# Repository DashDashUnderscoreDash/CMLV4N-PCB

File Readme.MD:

# **CMLV4N**

CMLV4N is an STM32 12u V4N style PCB with leafspring tadpole mounting featuring forced Cherry ML support

The goal of this PCB is to have a 40% keyboard that uses Cherry ML switches harvested from a Cherry G84-4100.

### PLEASE ENSURE YOU VERIFY THE SPACEBAR IS LARGE ENOUGH!!!! There are multiple models you can use for donor boards and some have too small of spacebar.

Due to the uneven u sizing on Cherry ML the enter key does not fill that entire area. The stabilizer positions for the enter also do not work as they are for a larger sized keycap. This is a compromise that needed to be made to make the layout work and a combination of skill issue. The stabilizer position on the enter does not work as the footprint is the incorrect size. Apologies!

~~Available~~ Sold out at [Dashkeebs](https://dashkeebs.bigcartel.com/product/cmlv4n-pcb) as of 10/1/26

### In this repo you will find:
```
- Layout options
- Images of PCB
- VIAL firmware
- STEP model of PCB
- Edgecuts of PCB
- Complete KiCad project
- Case files (STEP format)
```

VIAL firmware commissioned by [Moinboards.](https://moinboards.de/) Thank you again so much!

### KLC layout

### PCB images

### Case image

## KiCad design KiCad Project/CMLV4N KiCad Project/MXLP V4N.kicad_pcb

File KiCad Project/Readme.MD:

# **CMLV4N KiCad Project**

This is my first fully open source KiCad project!

Made in KiCad 9 as it's working well for me and I'm afraid to upgrade and break things

As of 10/3/26 everything uploads to JLC with no errors less needing to orient some components on JLCPCB
<br>
<br>
<br>
I'm not sure if anything else should be put in this readme, so apologies if any information is missing. Feel free to start an issue or DM me on Discord. Username: dashdashunderscoredash
<br>
<br>
<br>
Due to skill issue, when making production files, some components are not oriented correctly. When placing the components in JLC you will need to change:
__ __
- U4: Transient voltage suppressor
__ __
- U3: Over current protection
__ __

### Incorrect orientation

### Corrected orientation

<br>
<br>
<br>
**Credit:** Leafspring tadpole mount by HaiZeus. Thank you so much for sharing these with me, letting me use on my designs, and helping me learning to design in general. [Please check out his store](https://www.haikey.design/), he's a very talented designer!

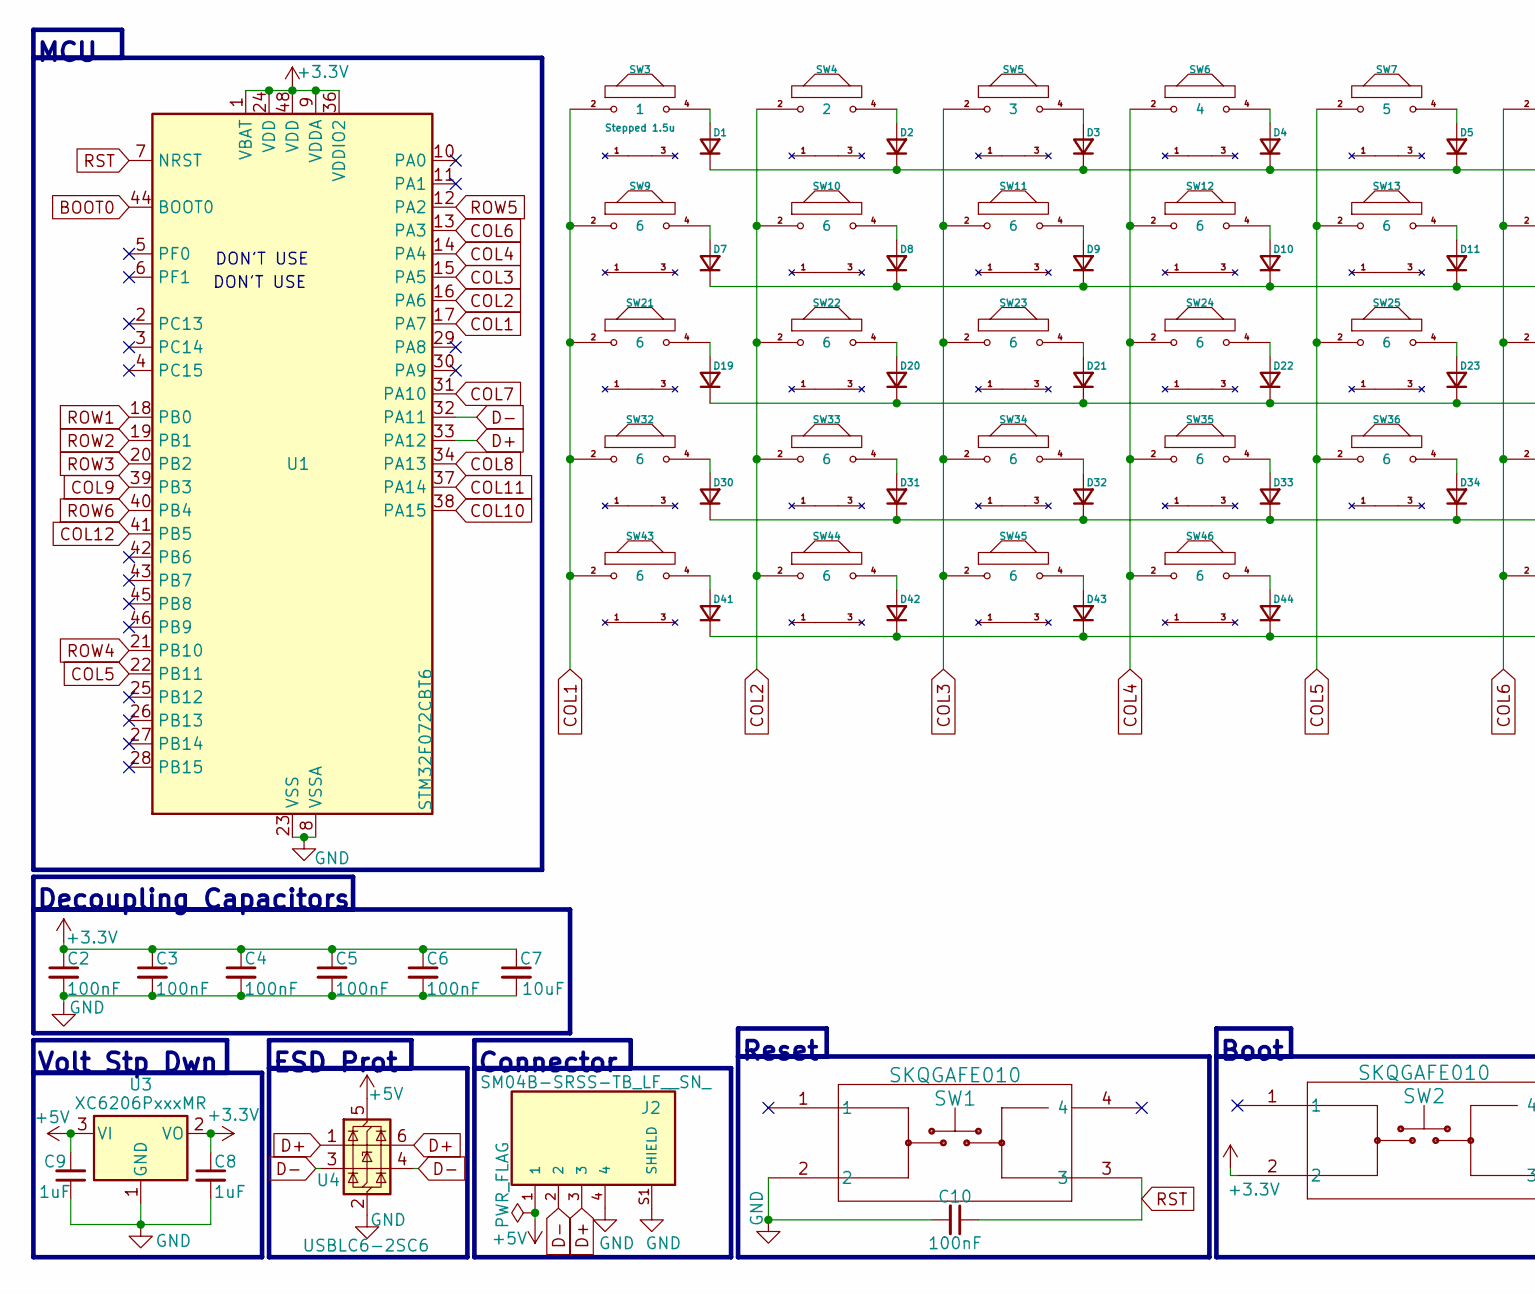
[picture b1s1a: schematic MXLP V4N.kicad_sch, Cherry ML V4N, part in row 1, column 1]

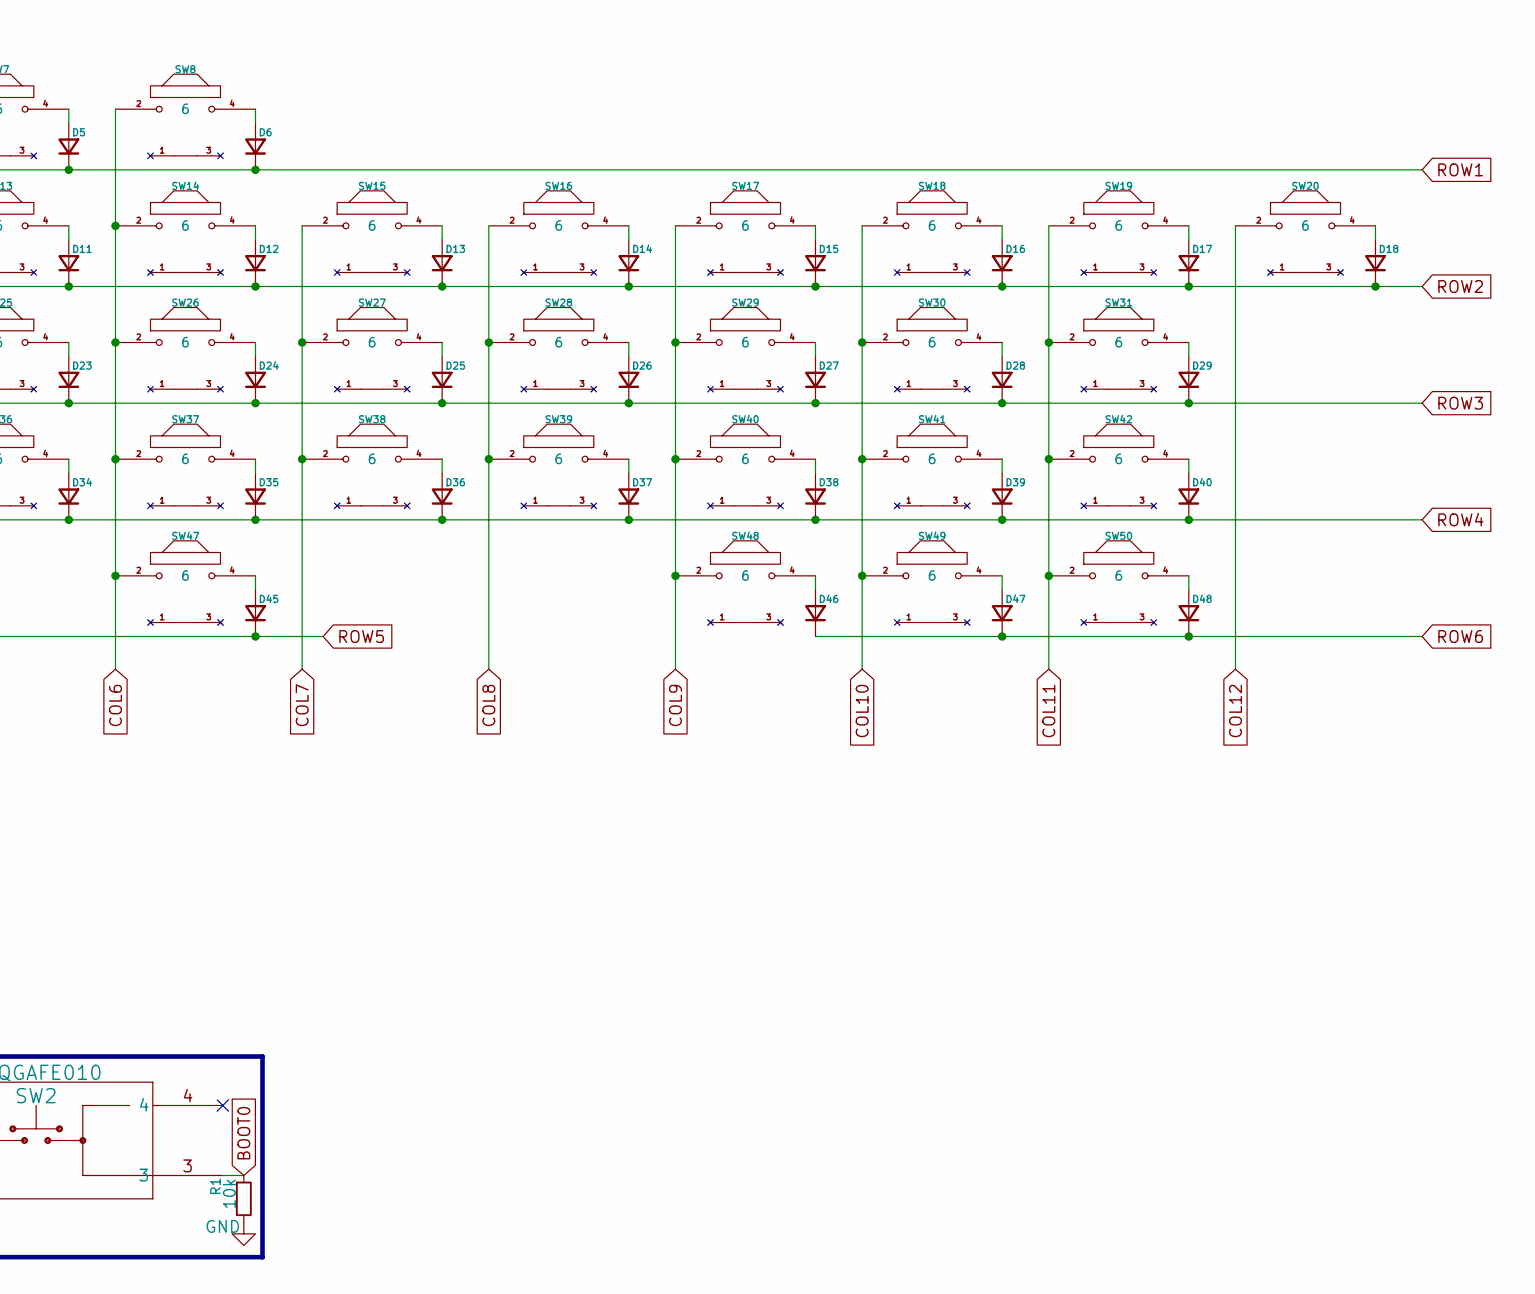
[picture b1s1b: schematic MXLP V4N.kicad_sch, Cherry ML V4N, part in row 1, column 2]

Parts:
C2, C3, C4, C5, C6: 100nF; C_0603_1608Metric; LCSC # C49678
C7: 10uF; C_0603_1608Metric; LCSC # C15850
C8, C9: 1uF; C_0603_1608Metric; LCSC # C28323
C10: 100nF; C_0603_1608Metric
D1, D2, D3, D4, D5, D6, D7, D8, D9, D10, D11, D12, D13, D14, D15, D16, D17, D18, D19, D20, D21, D22, D23, D24, D25, D26, D27, D28, D29, D30, D31, D32, D33, D34, D35, D36, D37, D38, D39, D40, D41, D42, D43, D44, D45, D46, D47, D48: D_Small; D_0603_1608Metric
J2: SM04B-SRSS-TB_LF__SN_; JST-SR-4; LCSC # C51940130
R1: 10k; R_0603_1608Metric; LCSC # C17414
SW1, SW2: SKQGAFE010; SW4_SKQGAFE010_ALPS; LCSC # C202424
SW3: 1; SW_Cherry_ML_1u_Centred_Wired_Correctly
SW4: 2; SW_Cherry_ML_1u_Centred_Wired_Correctly
SW5: 3; SW_Cherry_ML_1u_Centred_Wired_Correctly
SW6: 4; SW_Cherry_ML_1u_Centred_Wired_Correctly
SW7: 5; SW_Cherry_ML_1u_Centred_Wired_Correctly
SW8, SW9, SW10, SW11, SW12, SW13, SW14, SW15, SW16, SW17, SW18, SW19, SW20, SW21, SW22, SW23, SW24, SW25, SW26, SW27, SW28, SW29, SW30, SW31, SW32, SW33, SW34, SW35, SW36, SW37, SW38, SW39, SW40, SW41, SW42, SW43, SW44, SW45, SW46, SW47, SW48, SW49, SW50: 6; SW_Cherry_ML_1u_Centred_Wired_Correctly
U1: STM32F072CBT6; LQFP-48_7x7mm_P0.5mm; LCSC # C81720
U3: XC6206PxxxMR; SOT-23-3; LCSC # C5446
U4: USBLC6-2SC6; SOT-23-6; LCSC # C2687116

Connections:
+3.3V: C2.1, C3.1, C4.1, C5.1, C6.1, C7.1, C8.1, SW2.2, U1.1 (VBAT), U1.9 (VDDA), U1.24 (VDD), U1.36 (VDDIO2), U1.48 (VDD), U3.2 (VO)
+5V: C9.2, J2.1, U3.3 (VI), U4.5 (VBUS)
BOOT0: R1.1, SW2.3, U1.44 (BOOT0)
COL1: SW3.2, SW9.2, SW21.2, SW32.2, SW43.2, U1.17 (PA7)
COL2: SW4.2, SW10.2, SW22.2, SW33.2, SW44.2, U1.16 (PA6)
COL3: SW5.2, SW11.2, SW23.2, SW34.2, SW45.2, U1.15 (PA5)
COL4: SW6.2, SW12.2, SW24.2, SW35.2, SW46.2, U1.14 (PA4)
COL5: SW7.2, SW13.2, SW25.2, SW36.2, U1.22 (PB11)
COL6: SW8.2, SW14.2, SW26.2, SW37.2, SW47.2, U1.13 (PA3)
COL7: SW15.2, SW27.2, SW38.2, U1.31 (PA10)
COL8: SW16.2, SW28.2, SW39.2, U1.34 (PA13)
COL9: SW17.2, SW29.2, SW40.2, SW48.2, U1.39 (PB3)
COL10: SW18.2, SW30.2, SW41.2, SW49.2, U1.38 (PA15)
COL11: SW19.2, SW31.2, SW42.2, SW50.2, U1.37 (PA14)
COL12: SW20.2, U1.41 (PB5)
D+: J2.3, U1.33 (PA12), U4.1 (I/O1), U4.6 (I/O1)
D-: J2.2, U1.32 (PA11), U4.3 (I/O2), U4.4 (I/O2)
GND: C2.2, C3.2, C4.2, C5.2, C6.2, C7.2, C8.2, C9.1, C10.2, J2.4, J2.S1 (SHIELD), J2.S2 (SHIELD), R1.2, SW1.2, U1.8 (VSSA), U1.23 (VSS), U1.35 (VSS), U1.47 (VSS), U3.1 (GND), U4.2 (GND)
unnamed: D1.2 (A), SW3.4
unnamed: D2.2 (A), SW4.4
unnamed: D3.2 (A), SW5.4
unnamed: D4.2 (A), SW6.4
unnamed: D5.2 (A), SW7.4
unnamed: D6.2 (A), SW8.4
unnamed: D7.2 (A), SW9.4
unnamed: D8.2 (A), SW10.4
unnamed: D9.2 (A), SW11.4
unnamed: D10.2 (A), SW12.4
unnamed: D11.2 (A), SW13.4
unnamed: D12.2 (A), SW14.4
unnamed: D13.2 (A), SW15.4
unnamed: D14.2 (A), SW16.4
unnamed: D15.2 (A), SW17.4
unnamed: D16.2 (A), SW18.4
unnamed: D17.2 (A), SW19.4
unnamed: D18.2 (A), SW20.4
unnamed: D19.2 (A), SW21.4
unnamed: D20.2 (A), SW22.4
unnamed: D21.2 (A), SW23.4
unnamed: D22.2 (A), SW24.4
unnamed: D23.2 (A), SW25.4
unnamed: D24.2 (A), SW26.4
unnamed: D25.2 (A), SW27.4
unnamed: D26.2 (A), SW28.4
unnamed: D27.2 (A), SW29.4
unnamed: D28.2 (A), SW30.4
unnamed: D29.2 (A), SW31.4
unnamed: D30.2 (A), SW32.4
unnamed: D31.2 (A), SW33.4
unnamed: D32.2 (A), SW34.4
unnamed: D33.2 (A), SW35.4
unnamed: D34.2 (A), SW36.4
unnamed: D35.2 (A), SW37.4
unnamed: D36.2 (A), SW38.4
unnamed: D37.2 (A), SW39.4
unnamed: D38.2 (A), SW40.4
unnamed: D39.2 (A), SW41.4
unnamed: D40.2 (A), SW42.4
unnamed: D41.2 (A), SW43.4
unnamed: D42.2 (A), SW44.4
unnamed: D43.2 (A), SW45.4
unnamed: D44.2 (A), SW46.4
unnamed: D45.2 (A), SW47.4
unnamed: D46.2 (A), SW48.4
unnamed: D47.2 (A), SW49.4
unnamed: D48.2 (A), SW50.4
ROW1: D1.1 (K), D2.1 (K), D3.1 (K), D4.1 (K), D5.1 (K), D6.1 (K), U1.18 (PB0)
ROW2: D7.1 (K), D8.1 (K), D9.1 (K), D10.1 (K), D11.1 (K), D12.1 (K), D13.1 (K), D14.1 (K), D15.1 (K), D16.1 (K), D17.1 (K), D18.1 (K), U1.19 (PB1)
ROW3: D19.1 (K), D20.1 (K), D21.1 (K), D22.1 (K), D23.1 (K), D24.1 (K), D25.1 (K), D26.1 (K), D27.1 (K), D28.1 (K), D29.1 (K), U1.20 (PB2)
ROW4: D30.1 (K), D31.1 (K), D32.1 (K), D33.1 (K), D34.1 (K), D35.1 (K), D36.1 (K), D37.1 (K), D38.1 (K), D39.1 (K), D40.1 (K), U1.21 (PB10)
ROW5: D41.1 (K), D42.1 (K), D43.1 (K), D44.1 (K), D45.1 (K), U1.12 (PA2)
ROW6: D46.1 (K), D47.1 (K), D48.1 (K), U1.40 (PB4)
RST: C10.1, SW1.3, U1.7 (NRST)

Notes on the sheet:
Decoupling Capacitors
DON'T USE
ESD Prot
Boot
Connector
Volt Stp Dwn
Reset
MCU

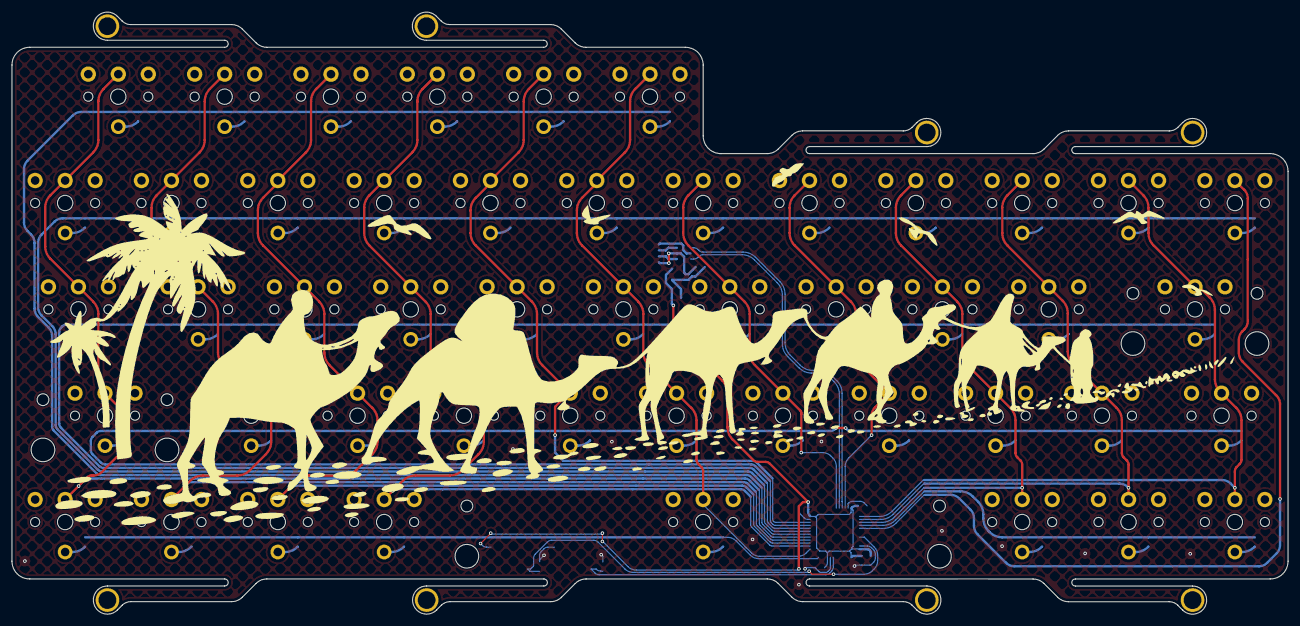
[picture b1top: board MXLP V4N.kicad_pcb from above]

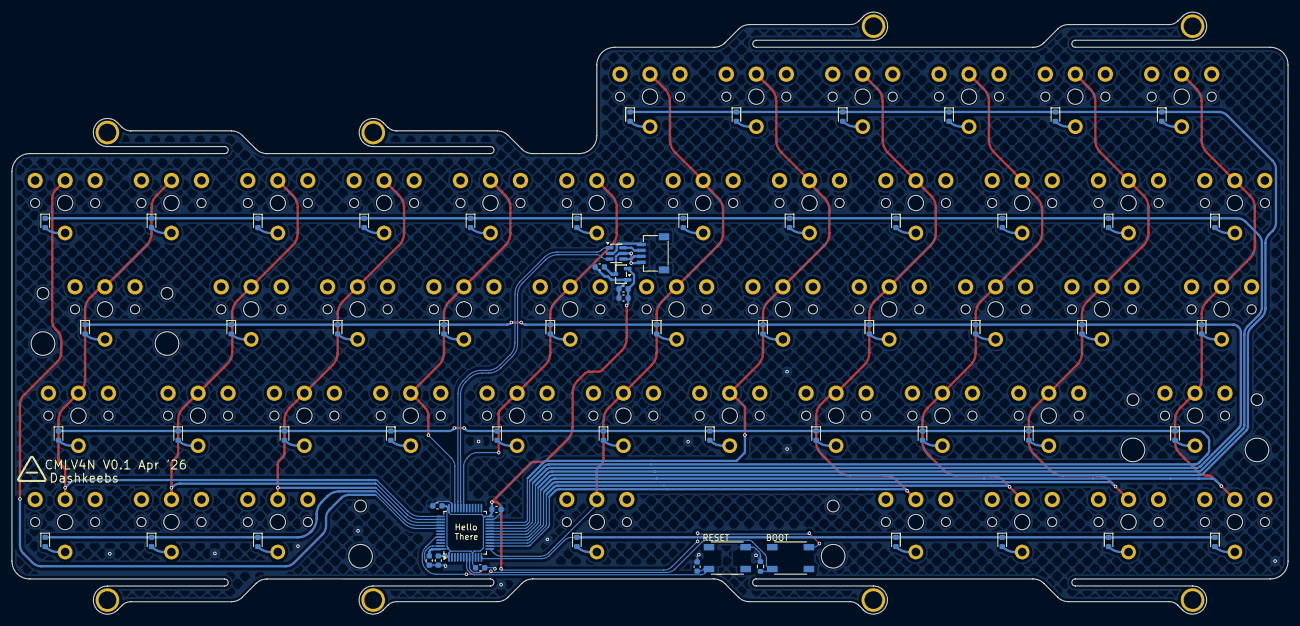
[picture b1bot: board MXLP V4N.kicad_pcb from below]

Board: 2 copper layers, 216.0 x 101.9 mm, 120 parts (64 on the bottom side), 73 nets.

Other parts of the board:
Ref**: Tadpole_Flex; HaiZeus_Tadpole_Flex
Ref**#2, Ref**#4, Ref**#7: Tadpole_Flex; HaiZeus_Tadpole_Flex
Ref**#3, Ref**#5, Ref**#6, Ref**#8: Tadpole_Flex; HaiZeus_Tadpole_Flex_Flipped

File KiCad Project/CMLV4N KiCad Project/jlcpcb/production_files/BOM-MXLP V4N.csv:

Comment,Designator,Footprint,LCSC,Quantity
100nF,"C10,C2,C3,C4,C5,C6",C_0603_1608Metric,C282519,6
10k,R1,R_0603_1608Metric,C2930027,1
10uF,C7,C_0603_1608Metric,C19702,1
1uF,"C8,C9",C_0603_1608Metric,C1592,2
D_Small,"D1,D10,D11,D12,D13,D14,D15,D16,D17,D18,D19,D2,D20,D21,D22,D23,D24,D25,D26,D27,D28,D29,D3,D30,D31,D32,D33,D34,D35,D36,D37,D38,D39,D4,D40,D41,D42,D43,D44,D45,D46,D47,D48,D5,D6,D7,D8,D9",D_0603_1608Metric,C30584800,48
SKQGAFE010,"SW1,SW2",SW4_SKQGAFE010_ALPS,C202424,2
SM04B-SRSS-TB_LF__SN_,J2,JST-SR-4,C51940130,1
STM32F072CBT6,U1,LQFP-48_7x7mm_P0.5mm,C81720,1
USBLC6-2SC6,U4,SOT-23-6,C2687116,1
XC6206PxxxMR,U3,SOT-23-3,C5446,1
